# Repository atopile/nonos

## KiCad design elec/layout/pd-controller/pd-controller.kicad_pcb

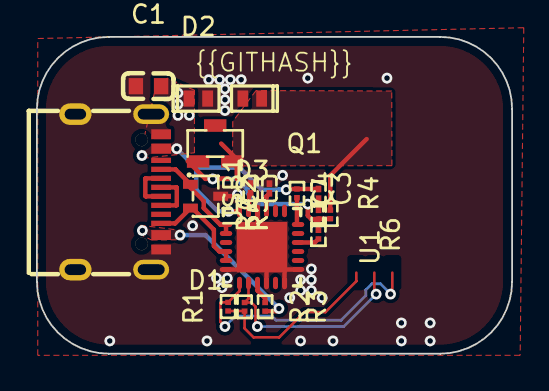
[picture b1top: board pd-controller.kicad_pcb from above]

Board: 2 copper layers, 26.4 x 17.6 mm, 17 parts (0 on the bottom side), 17 nets.

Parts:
C1: 4.7µF ±10% 35V X5R; C0603
C2: 100nF ±10% 10V X5R; C0201
C3: C0201
C4: 1µF ±20% 6.3V X5R; C0201
D1: ESDA25W; SOT-323-3_L2.1-W1.3-P1.32-LS2.1-BR
D2, D3: DFN1610-2_L1.6-W1.0-P1.05-RD
Q1: MOSFET; SOT-23-3_L2.9-W1.3-P1.90-LS2.4-BR
R1: 1kΩ ±1% 50mW; R0201
R2: 4.64kΩ ±1% 50mW; R0201
R3, R4: R0201
R5: 100kΩ ±1% 50mW; R0201
R6: 22.1kΩ ±1% 50mW; R0201
R7: 100Ω ±1% 50mW; R0201
U1: STUSB4500QTR; QFN-24_L4.0-W4.0-P0.50-BL-EP2.8
USB1: TYPE_C_16PIN_2MD073; USB-C-SMD_TYPE-C-6PIN-2MD-073

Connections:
CC1: D1.1, U1.1, U1.2, USB1.4
CC2: D1.2, U1.4, U1.5, USB1.10
I2C_SCL: R2.1, U1.7
I2C_SDA: R3.1, U1.8
USB_CONNECTOR-net: USB1.6, USB1.8
USB_CONNECTOR-net-1: USB1.5, USB1.7
VBUS: C1.2, C2.2, D2.1, Q1.2, R1.1, R4.1, U1.24, USB1.2, USB1.11
VREG_1V2: C3.2, U1.21
VREG_2V7: C4.2, U1.23
VSINK_VCC: D3.1, Q1.3, R5.2
hv: R2.2, R3.2
lv: C1.1, C3.1, C4.1, D1.3, D2.2, D3.2, U1.6, U1.10, U1.12, U1.13, U1.22, U1.25, USB1.1, USB1.12, USB1.13, USB1.14
net: C2.1, R7.2
net-1: Q1.1, R5.1, R6.1, R7.1
net-2: R4.2, U1.18
net-3: R1.2, U1.9
net-4: R6.2, U1.16

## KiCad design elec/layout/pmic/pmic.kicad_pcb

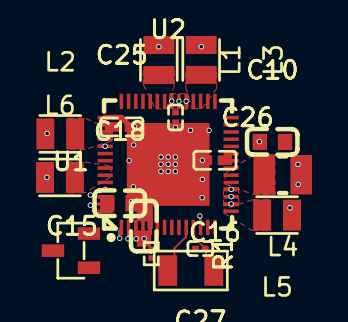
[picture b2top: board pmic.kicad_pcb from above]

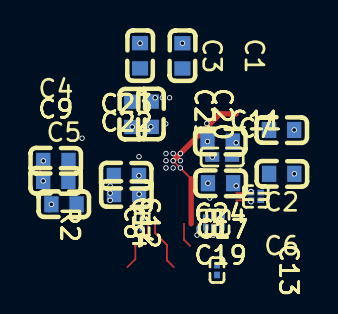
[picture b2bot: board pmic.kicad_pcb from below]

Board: 2 copper layers, 38 parts (21 on the bottom side), 25 nets.

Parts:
C1, C2, C3, C4, C5, C6: 22µF ±20% 6.3V X5R; C0603
C7, C8, C11, C12, C13, C14: 1µF ±20% 6.3V X5R; C0201
C9, C10: 4.7µF ±10% 16V X5R; C0603
C15, C18, C19, C20, C21, C22, C23, C24: 10µF ±10% 10V X5R; C0603
C16, C17, C25: 2.2µF ±20% 10V X5R; C0402
C26, C27: 10pF ±5% 50V C0G; C0201
L1, L2, L3, L5, L6: 470nH ±20% 3A - infA; IND-SMD_L2.0-W1.6
L4: 1µH ±20% 3A - infA; IND-SMD_L2.5-W2.0-1
R1: 10kΩ ±1% 50mW; R0201
R2: 1.5Ω ±5% 50mW; R0201
U1: LDO 1.2V Vin max 3.3V - infV Iq; SOT-23-3_L2.9-W1.3-P1.90-LS2.4-BR
U2: _PCA9450AAHNY; HVQFN-56_L7.0-W7.0-P0.40-BL-EP4.6
XTAL1: Crystal; OSC-SMD_L3.2-W1.5

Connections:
*F6F8-net-0: R2.2, U2.12
*F6F8-net-1: C26.1, U2.11, XTAL1.1
*F6F8-net-2: C27.1, U2.10, XTAL1.2
*F6F8-net-3: R1.1, U2.6
*F6F8.pmic-net: U2.48, U2.49
GND: C1.2, C2.2, C3.2, C4.2, C5.2, C6.2, C7.2, C8.2, C9.2, C10.2, C11.2, C12.2, C13.2, C14.2, C15.2, C16.2, C17.2, C18.2, C19.2, C20.2, C21.2, C22.2, C23.2, C24.2, C25.2, C26.2, C27.2, U1.1
NVCC_DRAM_1V1: C6.1, L6.2, U2.52
NVCC_SD2: C7.1, U2.55
NVCC_SNVS_1V8: C8.1, U2.3
VCC_3V3: C4.1, C9.1, C10.1, L4.2, R2.1, U1.3, U2.22, U2.23
VDDA_1V8: C11.1, U2.54
VDDA_1V8_SW: L6.1, U2.50, U2.51
VDD_1V8: C5.1, L5.2, U2.21
VDD_3V3_SW: L4.1, U2.19, U2.20
VDD_ARM_0V9: C2.1, L2.2
VDD_ARM_0V9_SW: L2.1, U2.45, U2.46
VDD_DRAM_0V9: C3.1, L3.2
VDD_DRAM_0V9_SW: L3.1, U2.31, U2.32
VDD_PHY_0V9: C12.1, U2.1
VDD_PHY_0V9_SW: L5.1, U2.15
VDD_PHY_1V2: C13.1, U1.2
VDD_SNVS_0V8: C14.1, U2.2
VDD_SOC_0V8: C1.1, L1.2
VDD_SOC_0V8_SW: L1.1, U2.36, U2.37
VSYS_5V: C15.1, C16.1, C17.1, C18.1, C19.1, C20.1, C21.1, C22.1, C23.1, C24.1, C25.1, U2.16, U2.17, U2.18, U2.33, U2.34, U2.35, U2.47, U2.56

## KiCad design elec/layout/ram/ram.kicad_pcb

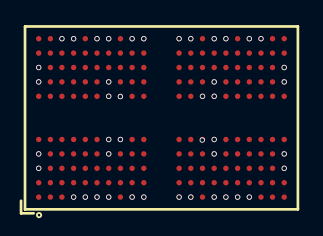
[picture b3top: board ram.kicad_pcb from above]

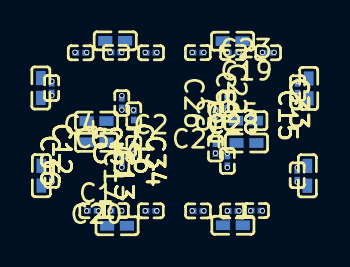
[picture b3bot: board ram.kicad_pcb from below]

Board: 2 copper layers, 37 parts (36 on the bottom side), 5 nets, no tracks yet.

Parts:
C1, C17, C18, C19, C20, C21, C22, C23, C25, C29, C30, C31: 10µF ±20% 6.3V X5R; C0402
C2, C3, C4, C5, C6, C7, C8, C9, C10, C11, C12, C13, C14, C15, C16, C24, C26, C27, C28, C32, C33, C34, C35, C36: 220nF ±20% 6.3V X5R; C0201
U1: _SK_HYNIX_H9HCNNNBKUMLXR_NEE; FBGA-200_L15.0-W10.0-BL_H9HCNNNBKUMLXR

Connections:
*3278-net: C25.1, C26.1, C27.1, C28.1, C29.1, C30.1, C31.1, C32.1, C33.1, C34.1, C35.1, C36.1, U1.F1, U1.F12, U1.G4, U1.G9, U1.T4, U1.T9, U1.U1, U1.U12
*3278.RAM-net-0: U1.A1, U1.A2, U1.A11, U1.A12, U1.AA1, U1.AA12, U1.AB1, U1.AB2, U1.AB11, U1.AB12, U1.B1, U1.B12
*3278.RAM-net-1: U1.A8, U1.G11, U1.H3, U1.J5, U1.K5, U1.K8, U1.N5, U1.N8, U1.P5, U1.R3
hv: C1.1, C2.1, C3.1, C4.1, C5.1, C6.1, C7.1, C8.1, C9.1, C10.1, C11.1, C12.1, C13.1, C14.1, C15.1, C16.1, C17.1, C18.1, C19.1, C20.1, C21.1, C22.1, C23.1, C24.1, U1.A4, U1.A9, U1.AA3, U1.AA5, U1.AA8, U1.AA10, U1.AB4, U1.AB9, U1.B3, U1.B5, U1.B8, U1.B10, U1.D1, U1.D5, U1.D8, U1.D12, U1.F3, U1.F5, U1.F8, U1.F10, U1.G2, U1.H1, U1.H5, U1.H8, U1.H12, U1.K1, U1.K3, U1.K10, U1.K12, U1.N1, U1.N3, U1.N10, U1.N12, U1.R1, U1.R5, U1.R8, U1.R12, U1.T2, U1.U3, U1.U5, U1.U8, U1.U10, U1.W1, U1.W5, U1.W8, U1.W12
lv: C1.2, C2.2, C3.2, C4.2, C5.2, C6.2, C7.2, C8.2, C9.2, C10.2, C11.2, C12.2, C13.2, C14.2, C15.2, C16.2, C17.2, C18.2, C19.2, C20.2, C21.2, C22.2, C23.2, C24.2, C25.2, C26.2, C27.2, C28.2, C29.2, C30.2, C31.2, C32.2, C33.2, C34.2, C35.2, C36.2, U1.A3, U1.A10, U1.AB3, U1.AB5, U1.AB8, U1.AB10, U1.C1, U1.C5, U1.C8, U1.C12, U1.D2, U1.D4, U1.D9, U1.D11, U1.E1, U1.E5, U1.E8, U1.E12, U1.G1, U1.G3, U1.G5, U1.G8, U1.G10, U1.G12, U1.J1, U1.J3, U1.J10, U1.J12, U1.K2, U1.K4, U1.K9, U1.K11, U1.N2, U1.N4, U1.N9, U1.N11, U1.P1, U1.P3, U1.P10, U1.P12, U1.T1, U1.T3, U1.T5, U1.T8, U1.T10, U1.T12, U1.V1, U1.V5, U1.V8, U1.V12, U1.W2, U1.W4, U1.W9, U1.W11, U1.Y1, U1.Y5, U1.Y8, U1.Y12

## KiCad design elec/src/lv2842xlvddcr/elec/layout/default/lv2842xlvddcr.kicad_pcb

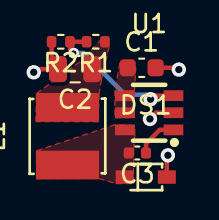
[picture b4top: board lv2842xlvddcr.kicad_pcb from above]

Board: 2 copper layers, 8 parts (0 on the bottom side), 6 nets.

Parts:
C1: 10V 10uF X5R ±10% 0603 Multilayer Ceramic Capacit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; C0603
C2: 25V 10uF X5R ±10% 0805 Multilayer Ceramic Capacit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; C0805
C3: 16V 100nF X7R ±10% 0402 Multilayer Ceramic Capaci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; C0402
DS1: SOD-323_L1.8-W1.3-LS2.5-RD
L1: IND-SMD_L4.0-W4.0
R1: 62.5mW Thick Film Resistors 50V ±100ppm/℃ ±1% 14.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; R0402
R2: 62.5mW Thick Film Resistors 50V ±100ppm/℃ ±1% 4.3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; R0402
U1: SOT-23-6_L2.9-W1.6-P0.95-LS2.8-BR

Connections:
cb: C3.1, U1.1
gnd: C1.2, C2.2, DS1.2, R2.2, U1.2
out: R1.2, R2.1, U1.3
sw: C3.2, DS1.1, L1.1, U1.6
vcc: C1.1, U1.4, U1.5
vcc-1: C2.1, L1.2, R1.1
